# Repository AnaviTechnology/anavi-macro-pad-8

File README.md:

# ANAVI Macro Pad 8

**Open source, programmable, eight-key keypad with backlighting, underlighting, and OLED screen**

ANAVI Macro Pad 8 is an open source, custom-programmable, mini 8-key keyboard/keypad. Each key can be reprogrammed to activate a macro or even a dedicated shortcut - all without any coding experience! Powered by the advanced, but easy-to-use [Quantum Mechanical Keyboard (QMK) open source firmware](https://github.com/qmk/qmk_firmware/tree/master/keyboards/anavi/macropad8).

ANAVI Macro Pad 8 has been designed with [the cross platform and open source electronics design automation suite KiCad](https://kicad.org/). [The acrylic enclosure](https://github.com/AnaviTechnology/anavi-cases/tree/master/anavi-macro-pad-8-case) has been designed with [OpenSCAD](https://www.openscad.org/).

[ANAVI Macro Pad 8 was successfully crowdfunded at Crowd Supply on 8 October 2020](https://www.crowdsupply.com/anavi-technology/anavi-macro-pad-8).

ANAVI Macro Pad 8 has been certified by [the Open Source Hardware Association under OSHWA UID BG000072 on July 13, 2020](https://certification.oshwa.org/bg000072.html).

For more details please visit https://anavi.technology/

# License

The project is released under the [Creative Commons Attribution-ShareAlike 4.0 International (CC BY-SA 4.0)](https://creativecommons.org/licenses/by-sa/4.0/).

Note: This is a human-readable summary of (and not a substitute for) the [license](https://creativecommons.org/licenses/by-sa/4.0/legalcode).

You are free to:

Share — copy and redistribute the material in any medium or format Adapt — remix, transform, and build upon the material for any purpose, even commercially. The licensor cannot revoke these freedoms as long as you follow the license terms. Under the following terms:

Attribution — You must give appropriate credit, provide a link to the license, and indicate if changes were made. You may do so in any reasonable manner, but not in any way that suggests the licensor endorses you or your use. ShareAlike — If you remix, transform, or build upon the material, you must distribute your contributions under the same license as the original. No additional restrictions — You may not apply legal terms or technological measures that legally restrict others from doing anything the license permits. Notices:

You do not have to comply with the license for elements of the material in the public domain or where your use is permitted by an applicable exception or limitation. No warranties are given. The license may not give you all of the permissions necessary for your intended use. For example, other rights such as publicity, privacy, or moral rights may limit how you use the material.

You will have to provide a link to the original creator of the project http://www.anavi.technology on any documentation or website.

Credit can be attributed through a link to the creator website: http://www.anavi.technology

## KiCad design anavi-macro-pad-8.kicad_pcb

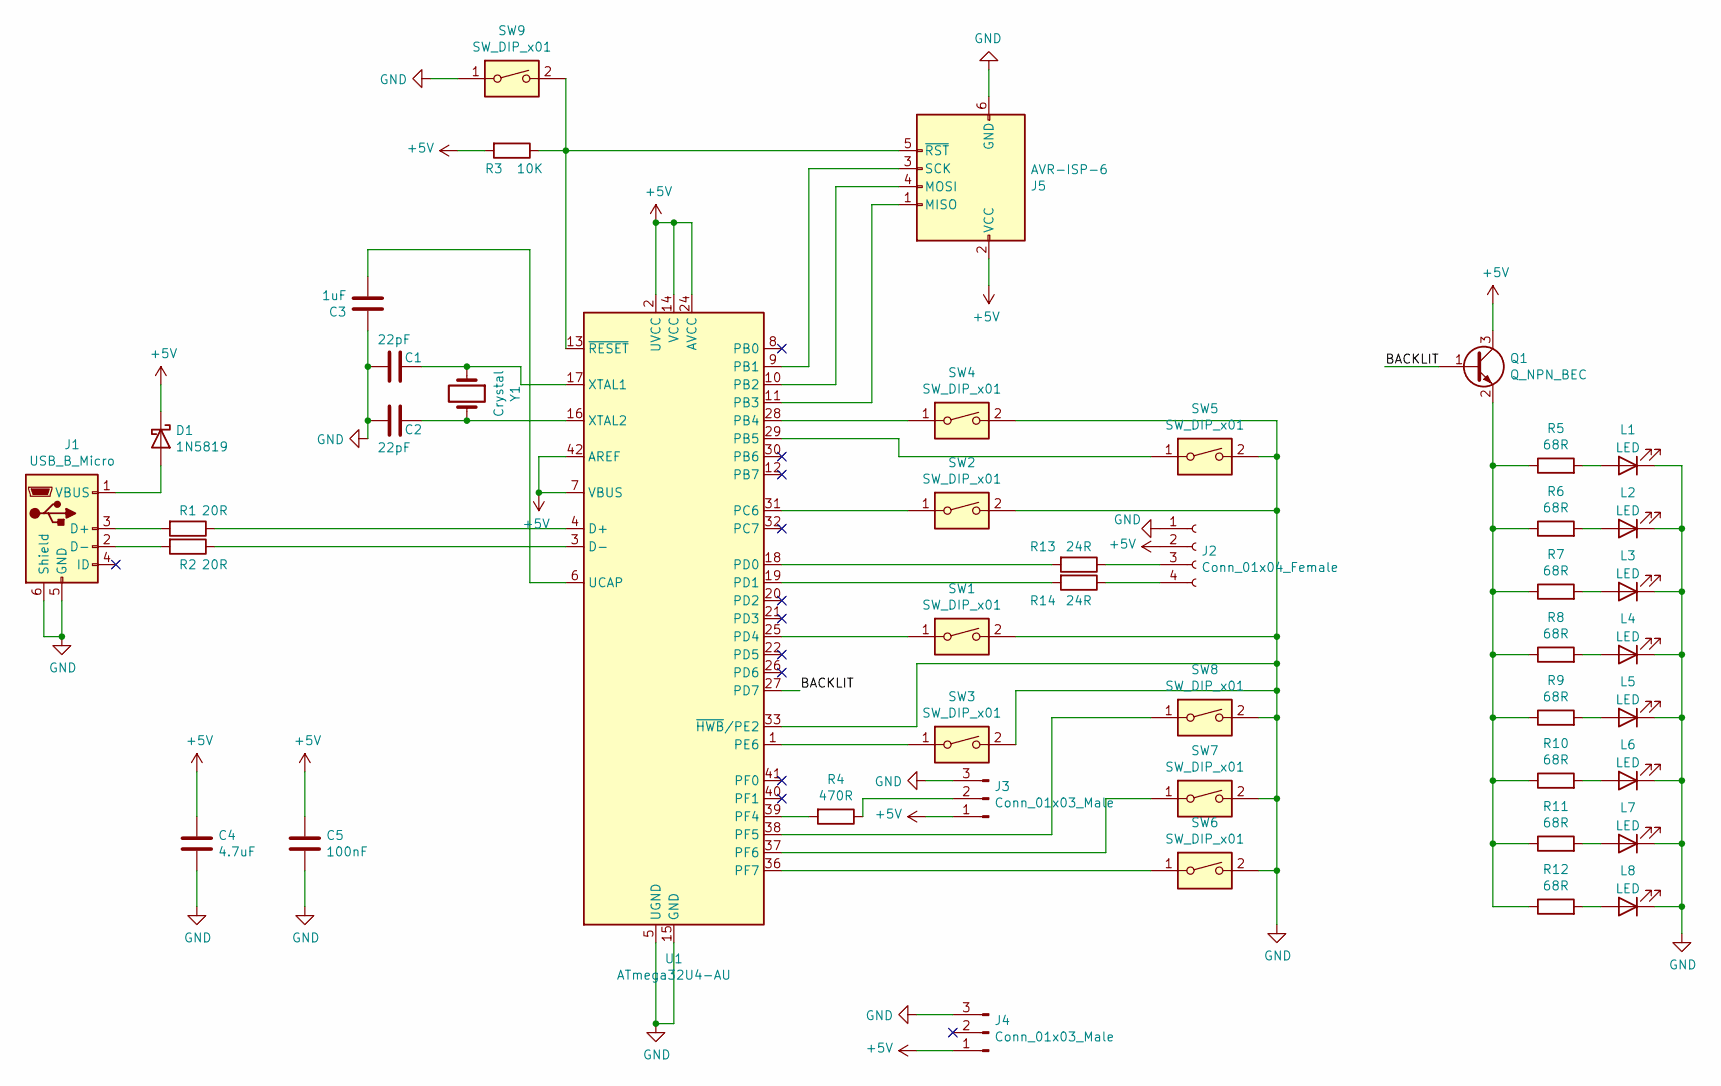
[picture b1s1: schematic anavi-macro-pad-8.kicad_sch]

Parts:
C1, C2: 22pF; C_0603_1608Metric
C3: 1uF; C_0603_1608Metric
C4: 4.7uF; C_0603_1608Metric
C5: 100nF; C_0603_1608Metric
D1: 1N5819; SMA_Standard
J1: USB_B_Micro; USB_Micro-B_Molex-105017-0001
J2: Conn_01x04_Female; PinHeader_1x04_P2.54mm_Vertical
J3, J4: Conn_01x03_Male; LedConnector_1x03_P2.54mm
J5: AVR-ISP-6; PinHeader_2x03_P2.54mm_Vertical
L1, L2, L3, L4, L5, L6, L7, L8: LED; LED_D3.0mm
Q1: Q_NPN_BEC; SOT-23
R1, R2: 20R; R_0603
R3: 10K; R_0603
R4: 470R; R_0603
R5, R6, R7, R8, R9, R10, R11, R12: 68R; R_0603
R13, R14: 24R; R_0603
SW1, SW2, SW3, SW4, SW5, SW6, SW7, SW8: SW_DIP_x01; SW_Cherry_MX_1.00u_Plate
SW9: SW_DIP_x01; SW_PUSH_6mm_h4.3mm
U1: ATmega32U4-AU; TQFP-44_10x10mm_P0.8mm
Y1: Crystal; Crystal_SMD_3225-4Pin_3.2x2.5mm_HandSoldering

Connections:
+5V: C4.1, C5.1, D1.1 (K), J2.2, J3.1, J4.1, J5.2 (VCC), Q1.3 (C), R3.2, U1.2 (UVCC), U1.7 (VBUS), U1.14 (VCC), U1.24 (AVCC), U1.34 (VCC), U1.42 (AREF), U1.44 (AVCC)
/BACKLIT: Q1.1 (B), U1.27 (PD7)
GND: C1.2, C2.2, C3.1, C4.2, C5.2, J1.5 (GND), J1.6 (Shield), J2.1, J3.3, J4.3, J5.6 (GND), L1.1 (K), L2.1 (K), L3.1 (K), L4.1 (K), L5.1 (K), L6.1 (K), L7.1 (K), L8.1 (K), SW1.2, SW2.2, SW3.2, SW4.2, SW5.2, SW6.2, SW7.2, SW8.2, SW9.1, U1.5 (UGND), U1.15 (GND), U1.23 (GND), U1.33 (~HWB/PE2), U1.35 (GND), U1.43 (GND); also elsewhere on the board
unnamed: C1.1, U1.17 (XTAL1), Y1.1
unnamed: C2.1, U1.16 (XTAL2), Y1.2
unnamed: C3.2, U1.6 (UCAP)
unnamed: D1.2 (A), J1.1 (VBUS)
unnamed: J1.2 (D-), R2.2
unnamed: J1.3 (D+), R1.2
unnamed: J2.3, R13.1
unnamed: J2.4, R14.1
unnamed: J3.2, R4.1
unnamed: J5.1 (MISO), U1.11 (PB3)
unnamed: J5.3 (SCK), U1.9 (PB1)
unnamed: J5.4 (MOSI), U1.10 (PB2)
unnamed 15: J5.5 (~RST), R3.1, SW9.2, U1.13 (~RESET); also elsewhere on the board
unnamed: L1.2 (A), R5.2
unnamed: L2.2 (A), R6.2
unnamed: L3.2 (A), R7.2
unnamed: L4.2 (A), R8.2
unnamed: L5.2 (A), R9.2
unnamed: L6.2 (A), R10.2
unnamed: L7.2 (A), R11.2
unnamed: L8.2 (A), R12.2
unnamed: Q1.2 (E), R5.1, R6.1, R7.1, R8.1, R9.1, R10.1, R11.1, R12.1
unnamed: R1.1, U1.4 (D+)
unnamed: R2.1, U1.3 (D-)
unnamed: R4.2, U1.39 (PF4)
unnamed: R13.2, U1.18 (PD0)
unnamed: R14.2, U1.19 (PD1)
unnamed: SW1.1, U1.25 (PD4)
unnamed: SW2.1, U1.31 (PC6)
unnamed: SW3.1, U1.1 (PE6)
unnamed: SW4.1, U1.28 (PB4)
unnamed: SW5.1, U1.29 (PB5)
unnamed: SW6.1, U1.36 (PF7)
unnamed: SW7.1, U1.37 (PF6)
unnamed: SW8.1, U1.38 (PF5)

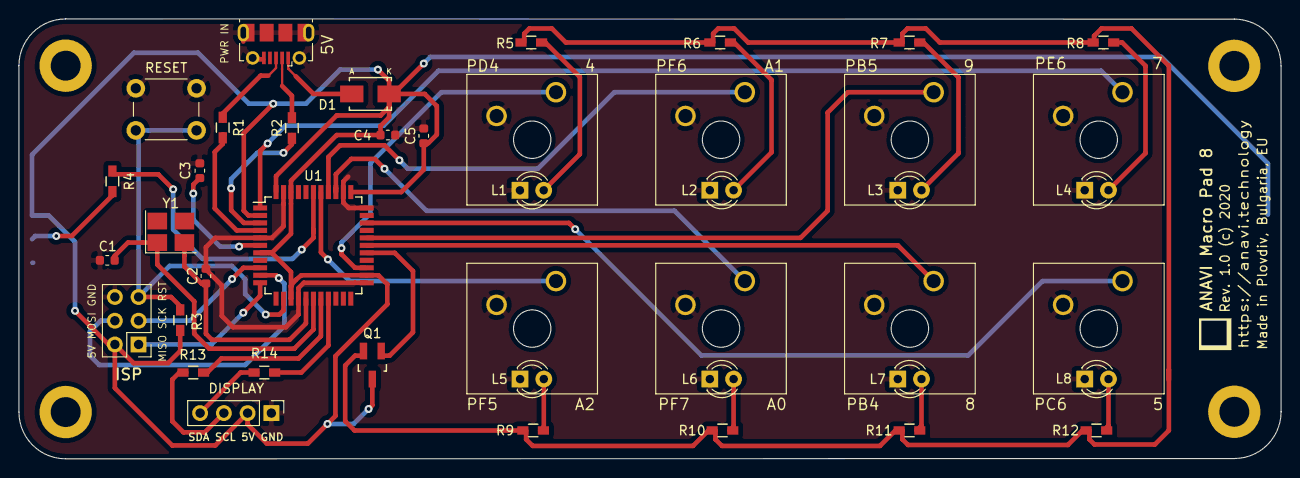
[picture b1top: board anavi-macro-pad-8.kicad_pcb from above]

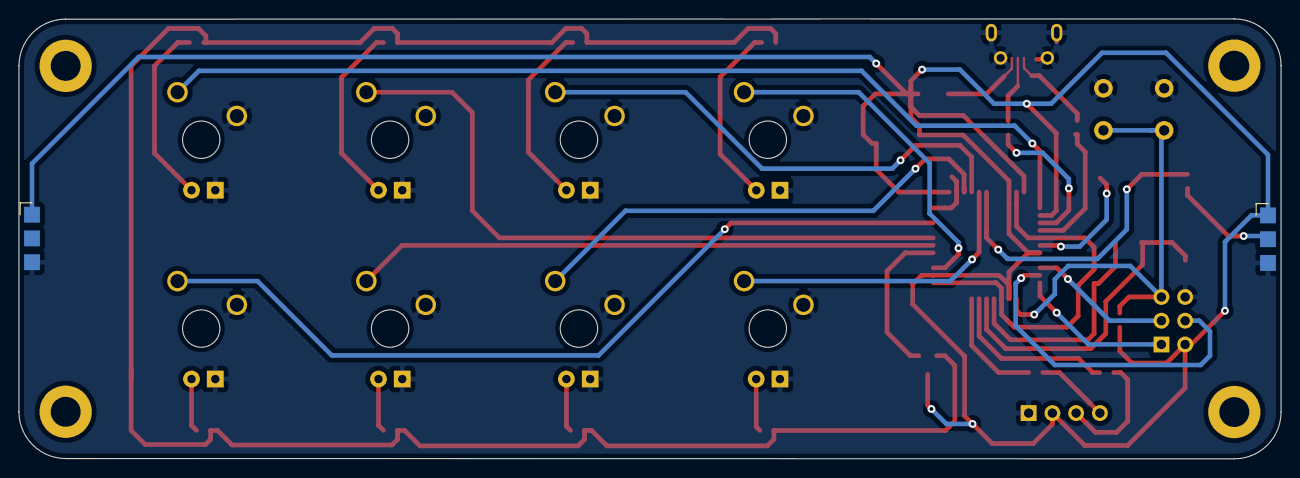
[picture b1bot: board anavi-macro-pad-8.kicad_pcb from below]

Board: 2 copper layers, 135.0 x 47.1 mm, 45 parts (2 on the bottom side), 38 nets.

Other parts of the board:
RESET: SW_DIP_x01; SW_PUSH_6mm_h4.3mm

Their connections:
GND: RESET.1; also elsewhere on the board
unnamed 15: RESET.2; also elsewhere on the board

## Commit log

2020-05-02 anavi-macro-pad-8: Initial commit
    Work in progress.
2020-05-03 Add outline and arrange components
2020-05-03 Add components to the schematics
    The following modificaitons to the schematics and the PCB have
    been done:
    * Added RESET button
    * Added pins for AVR SPI programmer
    * Changed the crystal footprint to 3225
    * Minor modificaitons to the PCB layouts
2020-05-03 anavi-macro-pad-8.kicad_pcb: Adjust LEDs
    Adjust the positions of the AVR SPI Programmer, the backlit
    LEDs and the resistors.
2020-05-03 anavi-macro-pad-8.kicad_pcb: Initial routing
    Work in progress on the routing of the PCB
2020-05-03 anavi-macro-pad-8: Routing with Schottky diode
    Add appropriate footprint for Schottky diode and complete the
    routing of the PCB.
2020-05-03 anavi-macro-pad-8.kicad_pcb: Add logo and labels
    Add logo and labels on the PCB.
2020-05-03 README.md: Add license
    Add README with a license.
2020-05-04 Minor improvements
2020-05-12 anavi-macro-pad-8: Improvements
    Rotate headers to match the direction of the addressable LED
    strip, update labels.
2020-05-19 anavi-macro-pad-8.kicad_pcb: Update silkscreen
    Update and improve labels on the front silkscreen.
2020-05-19 anavi-macro-pad-8.kicad_pcb: Update 5V labels
    Rotate the labels near the microUSB to match the direction of
    the other labels on the board.
2020-05-31 anavi-macro-pad-8.kicad_pcb: Change footprints
    Replace footprints for all resistors and the transistor with
    other same-sized footprints with bigger pads.
2020-10-27 anavi-macro-pad-8.jpg: Add image
    Add image of ANAVI Macro Pad 8
2020-10-27 README.md: Add notes about ANAVI Macro Pad 8
    Add short description about ANAVI Macro Pad 8 and the tools
    used to create it.
2020-10-27 README.md: Add OSHWA UID
    Add details about the OSHWA certification.
2021-11-08 Update README.md
    https://forum.kicad.info/t/warning-avoid-all-links-to-kicad-pcb-org-use-kicad-org/31521
2023-01-01 anavi-macro-pad-8: Convert from KiCad 5 to 6
    Convert the project from KiCad version 5 to version 6.
2023-01-01 anavi-macro-pad-8: Fix I2C protection resistors
    Resistors R13 and R14 had too large values. These are protection
    resistors used in series on the SDA and SCL lines of the I2C. To
    fix this issue the values of both resistors were set to 24 Ohms.
    fixes #4
    Reported-by: Heiko Lau <h.lau@ifam-erfurt.de>

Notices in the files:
anavi-macro-pad-8.kicad_pcb:
Rev. 1.0 (c) 2020
